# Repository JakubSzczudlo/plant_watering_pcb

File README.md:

# plant_watering_pcb
Kicad 8 PCB design for plant watering device with ESP32 as microprocessor

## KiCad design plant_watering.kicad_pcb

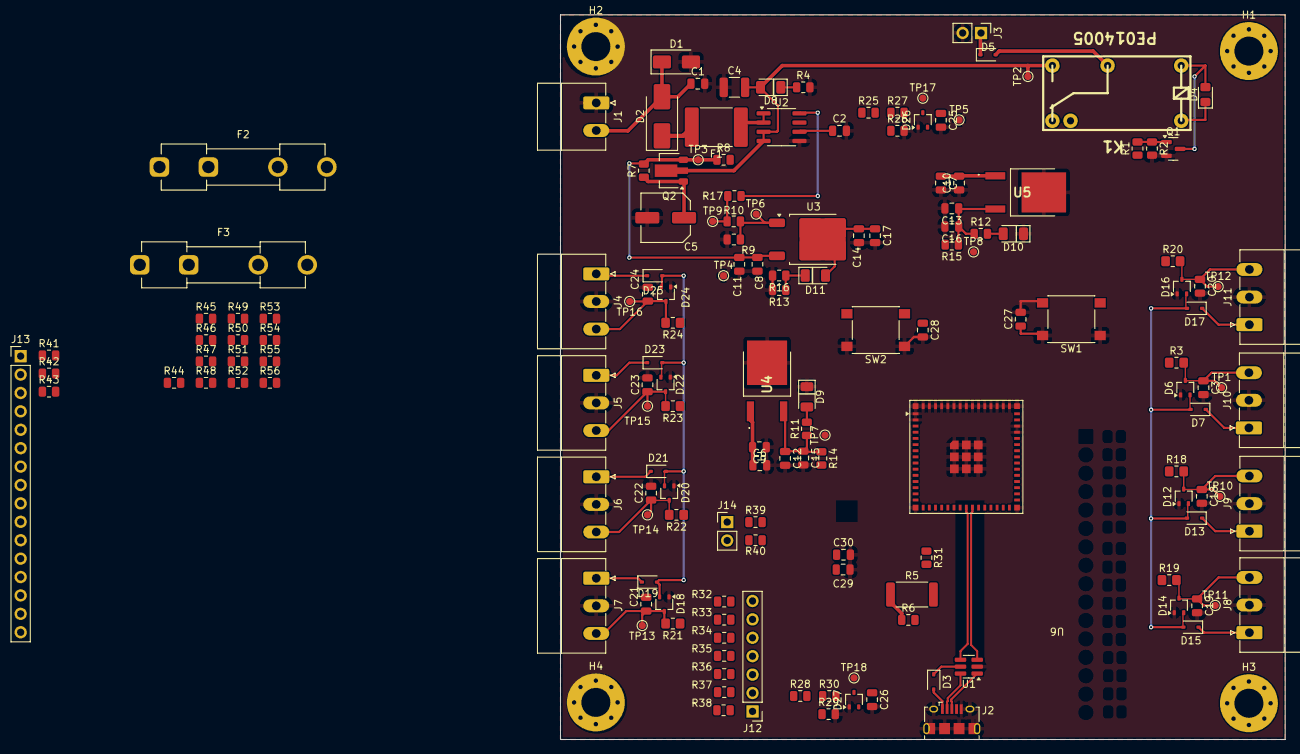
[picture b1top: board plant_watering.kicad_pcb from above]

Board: 4 copper layers, 100.0 x 100.0 mm, 163 parts (0 on the bottom side), 112 nets.

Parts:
C1, C9, C10, C11, C12, C13, C14, C27, C28, C30: 100nF 50V 10%; C_0805_2012Metric
C2, C25, C26: 1nF 50V 10%; C_0805_2012Metric
C3, C18, C19, C20, C21, C22, C23, C24: 10nF 50V 10%; C_0805_2012Metric
C4: 22uF 16V 10%; C_1210_3225Metric
C5: 47uF 50V; C_Elec_6.3x7.7
C6, C7, C8, C15, C16, C17: 4.7uF 25V 10%; C_0805_2012Metric
C29: 22uF 50V 10%; C_0805_2012Metric
D1: TGL34; D_SMA
D2: SK26-DIO; D_SMB_Handsoldering
D3, D5, D7, D13, D15, D17, D19, D21, D23, D25: 1N5817; D_SOD-323
D4: LL4148; D_0805_2012Metric_Pad1.15x1.40mm_HandSolder
D6, D12, D14, D16, D18, D20, D22, D24, D26, D27: BAT54SW; SOT-323_SC-70
D8, D9, D10, D11: LED_G; LED_1206_3216Metric_JLCPCB_Marking
F1: 2A; Fuse_2920_7451Metric
F2, F3: Fuse; Fuseholder_Clip-5x20mm_Keystone_3517_Inline_P23.11x6.76mm_D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
H1, H2, H3, H4: MountingHole; MountingHole_4mm_Pad_Via
J1: Conn_01x02; PhoenixContact_MC_1,5_2-G-3.81_1x02_P3.81mm_Horizontal
J2: USB_B_Micro; USB_Micro-B_Amphenol_10118194_Horizontal
J3, J14: Conn_01x02; PinHeader_1x02_P2.54mm_Vertical
J4, J5, J6, J7, J8, J9, J10, J11: Conn_01x03; PhoenixContact_MC_1,5_3-G-3.81_1x03_P3.81mm_Horizontal
J12: Conn_01x07; PinHeader_1x07_P2.54mm_Vertical
J13: Conn_01x16; PinHeader_1x16_P2.54mm_Vertical
K1: PE014005; relay_pe_hf
Q1: SSM3K72KFS,LF; SOT-23
Q2: BCX56TA; SOT-89-3
R1, R4, R6, R11, R12, R13, R16: 1k 5%; R_0805_2012Metric
R2, R31: 10k 5%; R_0805_2012Metric
R3, R18, R19, R20, R21, R22, R23, R24: 4.7k 5%; R_0805_2012Metric_Pad1.20x1.40mm_HandSolder
R5: DNF; R_2512_6332Metric
R7: DNF; R_0805_2012Metric
R8, R14, R15, R17: 0R; R_0805_2012Metric
R9: 75 1%; R_0805_2012Metric
R10: 232R; R_0805_2012Metric
R25, R28: 33k 0.1%; R_0805_2012Metric
R26, R29: 47k 0.1%; R_0805_2012Metric
R27, R30: 10k 0.1%; R_0805_2012Metric
R32, R33, R34, R35, R36, R37, R38, R39, R40, R41, R42, R43, R44, R45, R46, R47, R48, R49, R50, R51, R52, R53, R54, R55, R56: 22 5%; R_0805_2012Metric
SW1: SW_Boot; SW_Push_1P1T_NO_6x6mm_H9.5mm
SW2: SW_Enable; SW_Push_1P1T_NO_6x6mm_H9.5mm
TP1, TP2, TP3, TP4, TP5, TP6, TP7, TP8, TP9, TP10, TP11, TP12, TP13, TP14, TP15, TP16, TP17, TP18: TP; TestPoint_Pad_D1.0mm
U1: IP4234CZ6; SC-74-6_1.55x2.9mm_P0.95mm
U2: ACS712xLCTR-05B; SOIC-8_3.9x4.9mm_P1.27mm
U3: LM317_TO-252; TO-252-2
U4, U5: UA78M33IKVURG3
U6: ESP32-S3-MINI-1U; ESP32-S2-MINI-1U

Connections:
+3V3: C29.1, C30.1, D26.2, D27.2, R15.2, R31.2, U6.3 (3V3)
+3V3_Sens: D6.2, D7.2 (A), D12.2, D13.2 (A), D14.2, D15.2 (A), D16.2, D17.2 (A), D18.2, D19.2 (A), D20.2, D21.2 (A), D22.2, D23.2 (A), D24.2, D25.2 (A), R14.2
+5V: D4.1 (K), K1.2, R17.2, R28.1, U2.8 (VCC)
+12V: C4.2, D8.2 (A), K1.14, Q2.2 (C), R5.1, R6.1, TP2.1, U2.3 (IP-), U2.4 (IP-)
/5V_adc1/Input: R25.1, U2.7 (VIOUT)
/5V_adc1/Output: C25.1, D26.3, R27.2, TP17.1, U6.13 (IO9)
/5V_adc/Output: C26.1, D27.3, R30.2, TP18.1, U6.14 (IO10)
/ESP32/Relay: R1.1, U6.15 (IO11)
/ESP32/SENSOR_1: R24.1, U6.5 (IO1)
/ESP32/SENSOR_2: R23.1, U6.6 (IO2)
/ESP32/SENSOR_3: R22.1, U6.7 (IO3)
/ESP32/SENSOR_4: R21.1, U6.8 (IO4)
/ESP32/SENSOR_5: R19.1, U6.9 (IO5)
/ESP32/SENSOR_6: R18.1, U6.10 (IO6)
/ESP32/SENSOR_7: R3.1, U6.11 (IO7)
/ESP32/SENSOR_8: R20.1, U6.12 (IO8)
/ESP32/USB_N: U1.4, U6.23 (IO19)
/ESP32/USB_P: U1.3, U6.24 (IO20)
/USB+: J2.3 (D+), U1.1
/USB-: J2.2 (D-), U1.6
/sensor_connector4/3.3Vout: D17.1 (K), J11.1
/sensor_connector4/Vin: C20.1, D16.3, J11.3, R20.2, TP12.1
/sensor_connector5/3.3Vout: D7.1 (K), J10.1
/sensor_connector5/Vin: C3.1, D6.3, J10.3, R3.2, TP1.1
/sensor_connector6/3.3Vout: D13.1 (K), J9.1
/sensor_connector6/Vin: C18.1, D12.3, J9.3, R18.2, TP10.1
/sensor_connector7/3.3Vout: D15.1 (K), J8.1
/sensor_connector7/Vin: C19.1, D14.3, J8.3, R19.2, TP11.1
/sensor_connector8/3.3Vout: D19.1 (K), J7.1
/sensor_connector8/Vin: C21.1, D18.3, J7.3, R21.2, TP13.1
/sensor_connector9/3.3Vout: D21.1 (K), J6.1
/sensor_connector9/Vin: C22.1, D20.3, J6.3, R22.2, TP14.1
/sensor_connector10/3.3Vout: D23.1 (K), J5.1
/sensor_connector10/Vin: C23.1, D22.3, J5.3, R23.2, TP15.1
/sensor_connector11/3.3Vout: D25.1 (K), J4.1
/sensor_connector11/Vin: C24.1, D24.3, J4.3, R24.2, TP16.1
GND: C1.2, C2.2, C3.2, C4.1, C5.2, C6.2, C7.2, C8.2, C9.1, C10.1, C11.1, C12.2, C13.2, C14.2, C15.2, C16.2, C17.2, C18.2, C19.2, C20.2, C21.2, C22.2, C23.2, C24.2, C25.2, C26.2, C27.2, C28.2, C29.2, C30.2, D1.2 (A2), D5.2 (A), D6.1, D9.1 (K), D10.1 (K), D12.1, D14.1, D16.1, D18.1, D20.1, D22.1, D24.1, D26.1, D27.1, J1.1, J2.5 (GND), J2.6 (Shield), J3.2, J4.2, J5.2, J6.2, J7.2, J8.2, J9.2, J10.2, J11.2, Q1.2 (S), R2.2, R4.2, R10.1, R13.2, R16.2, R26.2, R29.2, SW1.1, SW2.1, TP4.1, TP5.1, U1.2 (VN), U2.5 (GND), U4.2 (GND), U5.2 (GND), U6.1 (GND), U6.2 (GND), U6.42 (GND), U6.43 (GND), U6.46 (GND), U6.47 (GND), U6.48 (GND), U6.49 (GND), U6.50 (GND), U6.51 (GND), U6.52 (GND), U6.53 (GND), U6.54 (GND), U6.55 (GND), U6.56 (GND), U6.57 (GND), U6.58 (GND), U6.59 (GND), U6.60 (GND), U6.61 (GND), U6.62 (GND), U6.63 (GND), U6.64 (GND), U6.65 (GND)
unnamed: C1.1, D1.1 (A1), D2.2 (A), J1.2
unnamed: D2.1 (K), F1.2
unnamed: D3.2 (A), J2.1 (VBUS)
unnamed: D3.1 (K), U1.5 (VP)
unnamed: D4.2 (A), K1.1, Q1.3 (D)
unnamed: D5.1 (K), J3.1, K1.11
unnamed: D8.1 (K), R4.1
unnamed: D9.2 (A), R11.2
unnamed: D10.2 (A), R12.2
unnamed: C14.1, C17.1, D11.2 (A), R9.2, R17.1, TP9.1, U3.2 (VO)
unnamed: D11.1 (K), R13.1, R16.1
unnamed: F1.1, U2.1 (IP+), U2.2 (IP+)
unnamed: J12.1, R38.2
unnamed: J12.2, R37.2
unnamed: J12.3, R36.2
unnamed: J12.4, R35.2
unnamed: J12.5, R34.2
unnamed: J12.6, R33.2
unnamed: J12.7, R32.2
unnamed: J13.1, R41.1
unnamed: J13.2, R42.1
unnamed: J13.3, R43.1
unnamed: J13.4, R44.1
unnamed: J13.5, R45.1
unnamed: J13.6, R46.1
unnamed: J13.7, R47.1
unnamed: J13.8, R48.1
unnamed: J13.9, R49.1
unnamed: J13.10, R50.1
unnamed: J13.11, R51.1
unnamed: J13.12, R52.1
unnamed: J13.13, R53.1
unnamed: J13.14, R54.1
unnamed: J13.15, R55.1
unnamed: J13.16, R56.1
unnamed: J14.1, R39.1
unnamed: J14.2, R40.1
unnamed: Q1.1 (G), R1.2, R2.1
unnamed: C5.1, Q2.1 (B), R5.2, R6.2, R7.1
unnamed: C8.1, C11.2, F2.1, F3.1, Q2.3 (E), R7.2, R8.1, TP3.1, U3.3 (VI)
unnamed: R25.2, R26.1, R27.1
unnamed: R28.2, R29.1, R30.1
unnamed: C2.1, U2.6 (FILTER)
unnamed: R9.1, R10.2, TP6.1, U3.1 (ADJ)
unnamed: C6.1, C9.2, F2.2, U4.1 (IN)
unnamed: C12.1, C15.1, R11.1, R14.1, TP7.1, U4.3 (OUT)
unnamed: C7.1, C10.2, F3.2, U5.1 (IN)
unnamed: C13.1, C16.1, R12.1, R15.1, TP8.1, U5.3 (OUT)
unnamed: C28.1, R31.1, SW2.2, U6.45 (EN)
unnamed: C27.1, SW1.2, U6.4 (IO0)
unnamed: R32.1, U6.16 (IO12)
unnamed: R33.1, U6.17 (IO13)
unnamed: R34.1, U6.18 (IO14)
unnamed: R35.1, U6.19 (IO15)
unnamed: R36.1, U6.20 (IO16)
unnamed: R37.1, U6.21 (IO17)
unnamed: R38.1, U6.22 (IO18)
unnamed: R41.2, U6.25 (IO21)
unnamed: R42.2, U6.26 (IO26)
unnamed: R43.2, U6.28 (IO33)
unnamed: R44.2, U6.29 (IO34)
unnamed: R45.2, U6.31 (IO35)
unnamed: R46.2, U6.32 (IO36)
unnamed: R47.2, U6.33 (IO37)
unnamed: R48.2, U6.34 (IO38)
unnamed: R49.2, U6.35 (IO39)
unnamed: R50.2, U6.36 (IO40)
unnamed: R51.2, U6.37 (IO41)
unnamed: R52.2, U6.38 (IO42)
unnamed: R53.2, U6.41 (IO45)
unnamed: R54.2, U6.44 (IO46)
unnamed: R55.2, U6.27 (IO47)
unnamed: R56.2, U6.30 (IO48)
unnamed: R40.2, U6.40 (RXD0)
unnamed: R39.2, U6.39 (TXD0)

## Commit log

2024-09-18 Add scheme for pcb.
